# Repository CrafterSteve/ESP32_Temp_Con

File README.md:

# ESP32_Temp_Con
An temperture control device, based on ESP32. With custom PCB board, it can fit an ESP32-DevKit as controller, DAC and ADC is done on board, as well as, a 5 to +-12v power supply.

## Notes:
项目中 ./main/my_spiffs/ 目录下的文件会通过命令，全部烧写的分区 label 的 flash 中。

创建自定义空间前，先做配置：
used "idf.py menuconfig" to change partition table to csv.

created "partitions.csv" with 256KB of spiffs as "/storage": （以下是"partitions.csv"文件应该包含的内容）
nvs, data, nvs, 0x9000, 0x6000
phy_init, data, phy, 0xf000, 0x1000
factory, app, factory, 0x10000, 0x100000
storage, data, spiffs, 0x110000, 0x40000

## SPIFFS指令：
使用时注意 python 工具的路径。“./” 代表本项目的根目录

python D:\esp\v5.2.1\esp-idf\components\partition_table\gen_esp32part.py .\partitions.csv .\partitions.bin                                      // 从csv生成分区文件

idf.py partition-table-flash                                                                                                                    // 烧录分区文件

python D:\esp\v5.2.1\esp-idf\components\spiffs\spiffsgen.py 0x40000 D:\esp_projects\dactest_2.1\main\my_spiffs my_spiffs_img                    // 创建SPIFFS镜像文件

python D:\esp\v5.2.1\esp-idf\components\partition_table\parttool.py -p COM3 write_partition --partition-name storage --input .\my_spiffs_img    // 写入esp32

## 程序调用
in code: base_path = "/storage"     // esp32内文件目录
"/storage/bmp_test.bmp" 为存入的文件
FILE *file = fopen("/storage/bmp_test.bmp", "rb");  // 如此打开flash上的文件
可通过 esp_spiffs_info(spiffs_conf.partition_label, &total, &used); 查看占用，检查是否写入。

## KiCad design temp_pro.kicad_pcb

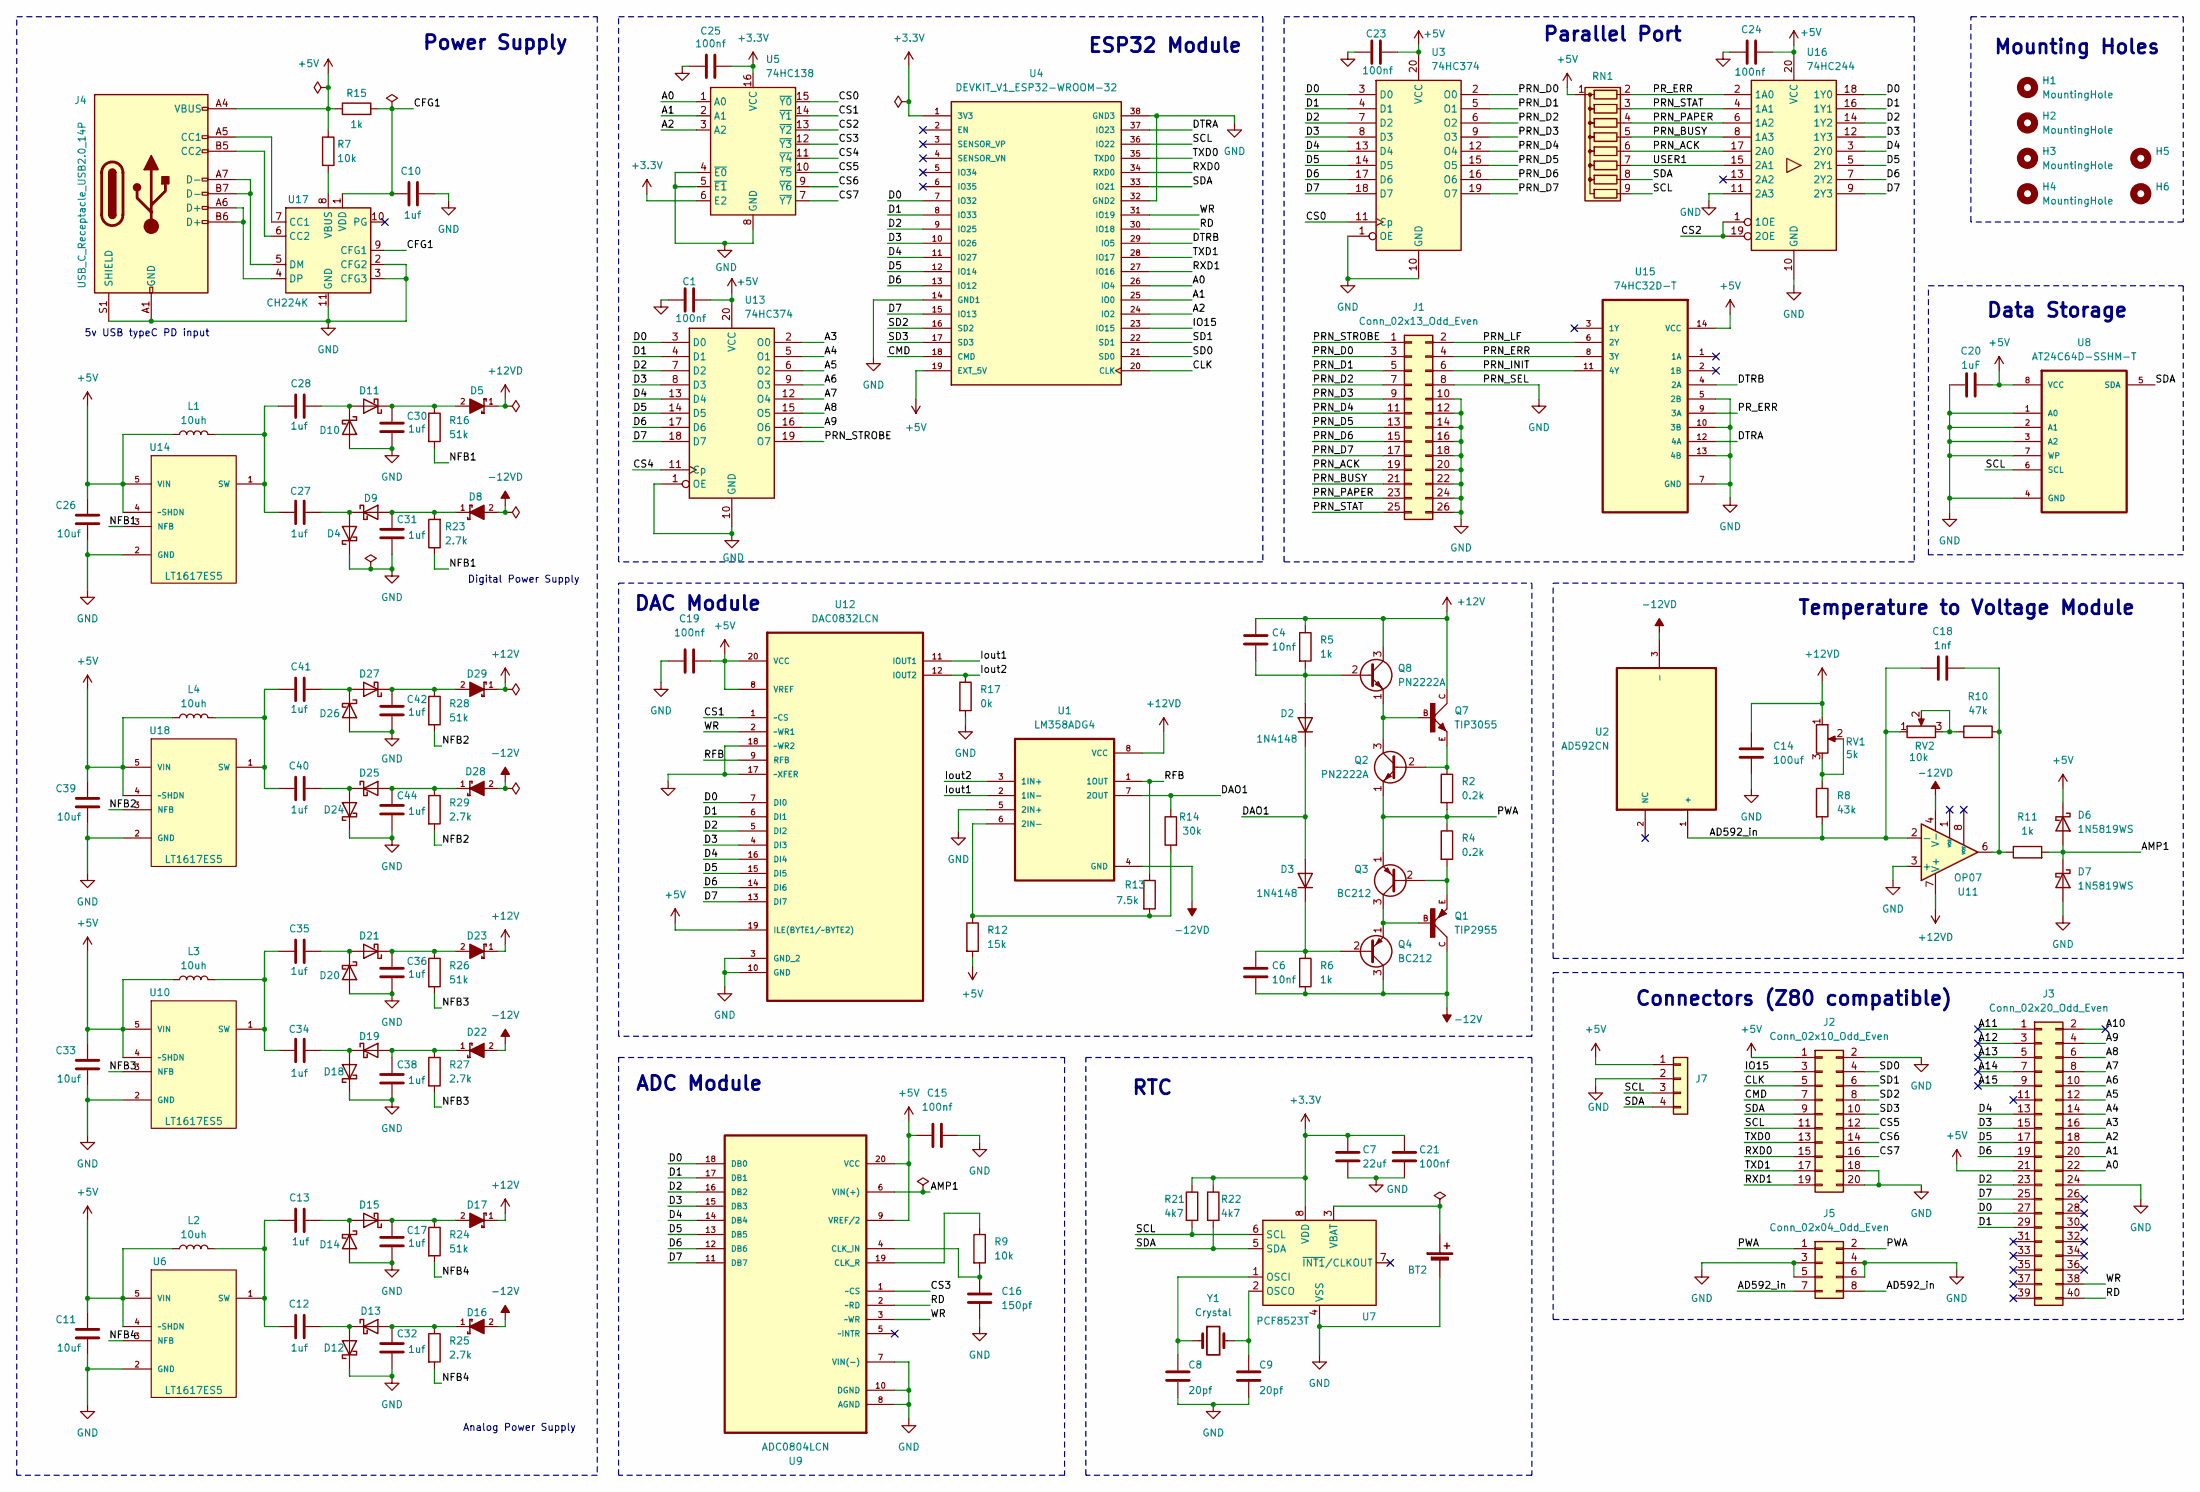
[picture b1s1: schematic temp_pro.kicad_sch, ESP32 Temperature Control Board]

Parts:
BT2: Battery_Cell; TE_796136-1
C1, C15, C19, C23, C24, C25: 100nf; C_0805_2012Metric
C4, C6: 10nf; C_Disc_D5.0mm_W2.5mm_P5.00mm
C7: 22uf; C_0805_2012Metric
C8, C9: 20pf; C_0805_2012Metric
C10: 1uf; C_0603_1608Metric
C11, C26, C33, C39: 10uf; C_0603_1608Metric
C12, C13, C17, C27, C28, C30, C31, C32, C34, C35, C36, C38, C40, C41, C42, C44: 1uf; C_0805_2012Metric
C14: 100uf; C_0805_2012Metric
C16: 150pf; C_0603_1608Metric
C18: 1nf; C_0805_2012Metric
C20: 1uF; C_0603_1608Metric
C21: 100nf; C_0603_1608Metric
D2, D3: 1N4148; D_DO-35_SOD27_P7.62mm_Horizontal
D4, D9, D10, D11, D12, D13, D14, D15, D18, D19, D20, D21, D24, D25, D26, D27: 1N5822; DIOM5025X220N
D5, D8, D16, D17, D22, D23, D28, D29: SS54-HF; DIOM5025X220N; MOUSER_PART_NUMBER 750-SS54-HF
D6, D7: 1N5819WS; D_SOD-323_HandSoldering
H1, H2, H3, H4, H5, H6: MountingHole; MountingHole_3.2mm_M3_ISO14580
J1: Conn_02x13_Odd_Even; PinHeader_2x13_P2.54mm_Vertical
J2: Conn_02x10_Odd_Even; PinHeader_2x10_P2.54mm_Vertical
J3: Conn_02x20_Odd_Even; PinHeader_2x20_P2.54mm_Vertical
J4: USB_C_Receptacle_USB2.0_14P; USB_C_Receptacle_GCT_USB4105-xx-A_16P_TopMnt_Horizontal
J5: Conn_02x04_Odd_Even; PinHeader_2x04_P2.54mm_Vertical
J7: Conn_01x04; PinHeader_1x04_P2.54mm_Vertical
L1, L2, L3, L4: 10uh; L_Bourns_SRP7028A_7.3x6.6mm
Q1: TIP2955; TOP3AV
Q2, Q8: PN2222A; TO-92_Inline
Q3, Q4: BC212; TO-92_Inline
Q7: TIP3055; TOP3AV
R2, R4: 0.2k; R_Axial_DIN0516_L15.5mm_D5.0mm_P20.32mm_Horizontal
R5, R6: 1k; R_Axial_DIN0207_L6.3mm_D2.5mm_P7.62mm_Horizontal
R7, R9: 10k; R_0603_1608Metric
R8: 43k; R_0805_2012Metric
R10: 47k; R_0805_2012Metric
R11, R15: 1k; R_0805_2012Metric
R12: 15k; R_0805_2012Metric
R13: 7.5k; R_0805_2012Metric
R14: 30k; R_0805_2012Metric
R16, R24, R26, R28: 51k; R_0603_1608Metric
R17: 0k; R_0603_1608Metric
R21, R22: 4k7; R_0603_1608Metric
R23, R25, R27, R29: 2.7k; R_0603_1608Metric
RN1: R_Network08; R_Array_SIP9
RV1: 5k; Potentiometer_Vishay_T93YA_Vertical
RV2: 10k; Potentiometer_Vishay_T93YA_Vertical
U1: LM358ADG4; DIP-8_W7.62mm_Socket
U2: AD592CN; TO-92L; MPN AD592CN
U3, U13: 74HC374; DIP-20_W7.62mm_Socket
U4: DEVKIT_V1_ESP32-WROOM-32; MODULE_DEVKIT_V1_ESP32-WROOM-32; PARTREV N/A
U5: 74HC138; DIP-16_W7.62mm_Socket
U6, U10, U14, U18: LT1617ES5; SOT-23-6; MPN LT1617ES5#PBF
U7: PCF8523T; SOIC-8_3.9x4.9mm_P1.27mm
U8: AT24C64D-SSHM-T; DIP-8_W7.62mm_Socket; MPN AT24C64D-SSHM-T
U9: ADC0804LCN; DIP-20_W7.62mm_Socket; MPN ADC0804LCN
U11: OP07; DIP-8_W7.62mm_Socket
U12: DAC0832LCN; DIP-20_W7.62mm_Socket; MPN DAC0832LCN
U15: 74HC32D-T; DIP-14_W7.62mm_Socket; MPN 74HC32D-T
U16: 74HC244; DIP-20_W7.62mm_Socket
U17: CH224K; SSOP-10-1EP_3.9x4.9mm_P1mm_EP2.1x3.3mm
Y1: Crystal; Crystal_C38-LF_D3.0mm_L8.0mm_Horizontal

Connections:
+3.3V: C7.1, C21.1, C25.2, R21.1, R22.1, U4.1 (3V3), U5.6 (E2), U5.16 (VCC), U7.8 (VDD)
+5V: C1.2, C11.1, C15.2, C19.2, C20.2, C23.2, C24.2, C26.1, C33.1, C39.1, D6.1 (K), J2.1, J3.21, J4.A4 (VBUS), J4.A9 (VBUS), J4.B4 (VBUS), J4.B9 (VBUS), J7.1, L1.1, L2.1, L3.1, L4.1, R7.1, R12.2, R15.1, RN1.1 (common), U3.20 (VCC), U4.19 (EXT_5V), U6.4 (~SHDN), U6.5 (VIN), U8.8 (VCC), U9.9 (VREF/2), U9.20 (VCC), U10.4 (~SHDN), U10.5 (VIN), U12.8 (VREF), U12.19 (ILE(BYTE1/~BYTE2)), U12.20 (VCC), U13.20 (VCC), U14.4 (~SHDN), U14.5 (VIN), U15.14 (VCC), U16.20 (VCC), U18.4 (~SHDN), U18.5 (VIN)
+12V: C4.1, D17.1, D23.1, D29.1, Q7.C, Q8.3 (C), R5.1
+12VD: C14.1, D5.1, RV1.1, U1.8 (VCC), U11.7 (V+)
-12V: C6.2, D16.2, D22.2, D28.2, Q1.C, Q4.3 (C), R6.2
-12VD: D8.2, U1.4 (GND), U2.3 (-), U11.4 (V-)
/A0: J3.22, U4.26 (IO4), U5.1 (A0)
/A1: J3.20, U4.25 (IO0), U5.2 (A1)
/A2: J3.18, U4.24 (IO2), U5.3 (A2)
/A3: J3.16, U13.2 (O0)
/A4: J3.14, U13.5 (O1)
/A5: J3.12, U13.6 (O2)
/A6: J3.10, U13.9 (O3)
/A7: J3.8, U13.12 (O4)
/A8: J3.6, U13.15 (O5)
/A9: J3.4, U13.16 (O6)
/A10: J3.2
/A11: J3.1
/A12: J3.3
/A13: J3.5
/A14: J3.7
/A15: J3.9
/AD592_in: C18.1, J5.7, J5.8, R8.2, RV2.1, U2.1 (+), U11.2 (-)
/AMP1: D6.2 (A), D7.1 (K), R11.2, U9.6 (VIN(+))
/CFG1: C10.1, R15.2, U17.1 (VDD), U17.9 (CFG1)
/CLK: J2.5, U4.20 (CLK)
/CMD: J2.7, U4.18 (CMD)
/CS0: U3.11 (Cp), U5.15 (~Y0)
/CS1: U5.14 (~Y1), U12.1 (~CS)
/CS2: U5.13 (~Y2), U16.1 (1OE), U16.19 (2OE)
/CS3: U5.12 (~Y3), U9.1 (~CS)
/CS4: U5.11 (~Y4), U13.11 (Cp)
/CS5: J2.12, U5.10 (~Y5)
/CS6: J2.14, U5.9 (~Y6)
/CS7: J2.16, U5.7 (~Y7)
/D0: J3.27, U3.3 (D0), U4.7 (IO32), U9.18 (DB0), U12.7 (DI0), U13.3 (D0), U16.18 (1Y0)
/D1: J3.29, U3.4 (D1), U4.8 (IO33), U9.17 (DB1), U12.6 (DI1), U13.4 (D1), U16.16 (1Y1)
/D2: J3.23, U3.7 (D2), U4.9 (IO25), U9.16 (DB2), U12.5 (DI2), U13.7 (D2), U16.14 (1Y2)
/D3: J3.15, U3.8 (D3), U4.10 (IO26), U9.15 (DB3), U12.4 (DI3), U13.8 (D3), U16.12 (1Y3)
/D4: J3.13, U3.13 (D4), U4.11 (IO27), U9.14 (DB4), U12.16 (DI4), U13.13 (D4), U16.3 (2Y0)
/D5: J3.17, U3.14 (D5), U4.12 (IO14), U9.13 (DB5), U12.15 (DI5), U13.14 (D5), U16.5 (2Y1)
/D6: J3.19, U3.17 (D6), U4.13 (IO12), U9.12 (DB6), U12.14 (DI6), U13.17 (D6), U16.7 (2Y2)
/D7: J3.25, U3.18 (D7), U4.15 (IO13), U9.11 (DB7), U12.13 (DI7), U13.18 (D7), U16.9 (2Y3)
/DAO1: D2.1 (K), D3.2 (A), R14.1, U1.7 (2OUT)
/DTRA: U4.37 (IO23), U15.12 (4A)
/DTRB: U4.29 (IO5), U15.4 (2A)
/IO15: J2.3, U4.23 (IO15)
/Iout1: U1.2 (1IN-), U12.11 (IOUT1)
/Iout2: R17.1, U1.3 (1IN+), U12.12 (IOUT2)
/NFB1: R16.2, R23.1, U14.3 (NFB)
/NFB2: R28.2, R29.2, U18.3 (NFB)
/NFB3: R26.2, R27.2, U10.3 (NFB)
/NFB4: R24.2, R25.2, U6.3 (NFB)
/PRN_ACK: J1.19, RN1.6 (R5), U16.17 (2A0)
/PRN_BUSY: J1.21, RN1.5 (R4), U16.8 (1A3)
/PRN_D0: J1.3, U3.2 (O0)
/PRN_D1: J1.5, U3.5 (O1)
/PRN_D2: J1.7, U3.6 (O2)
/PRN_D3: J1.9, U3.9 (O3)
/PRN_D4: J1.11, U3.12 (O4)
/PRN_D5: J1.13, U3.15 (O5)
/PRN_D6: J1.15, U3.16 (O6)
/PRN_D7: J1.17, U3.19 (O7)
/PRN_ERR: J1.4, U15.8 (3Y)
/PRN_INIT: J1.6, U15.11 (4Y)
/PRN_LF: J1.2, U15.6 (2Y)
/PRN_PAPER: J1.23, RN1.4 (R3), U16.6 (1A2)
/PRN_STAT: J1.25, RN1.3 (R2), U16.4 (1A1)
/PRN_STROBE: J1.1, U13.19 (O7)
/PR_ERR: RN1.2 (R1), U15.9 (3A), U16.2 (1A0)
/PWA: J5.1, J5.2, Q2.1 (E), Q3.1 (E), R2.2, R4.1
/RD: J3.40, U4.30 (IO18), U9.2 (~RD)
/RFB: R13.1, U1.1 (1OUT), U12.9 (RFB)
/RXD0: J2.15, U4.34 (RXD0)
/RXD1: J2.19, U4.27 (IO16)
/SCL: J2.11, J7.3, R21.2, RN1.9 (R8), U4.36 (IO22), U7.6 (SCL), U8.6 (SCL)
/SD0: J2.4, U4.21 (SD0)
/SD1: J2.6, U4.22 (SD1)
/SD2: J2.8, U4.16 (SD2)
/SD3: J2.10, U4.17 (SD3)
/SDA: J2.9, J7.4, R22.2, RN1.8 (R7), U4.33 (IO21), U7.5 (SDA), U8.5 (SDA)
/TXD0: J2.13, U4.35 (TXD0)
/TXD1: J2.17, U4.28 (IO17)
/USER1: RN1.7 (R6), U16.15 (2A1)
/WR: J3.38, U4.31 (IO19), U9.3 (~WR), U12.2 (~WR1)
GND: BT2.2 (-), C1.1, C7.2, C8.2, C9.2, C10.2, C11.2, C14.2, C15.1, C16.2, C17.2, C19.1, C20.1, C21.2, C23.1, C24.1, C25.1, C26.2, C30.2, C31.2, C32.2, C33.2, C36.2, C38.2, C39.2, C42.2, C44.2, D4.1 (K), D7.2 (A), D10.2 (A), D12.1 (K), D14.2 (A), D18.1 (K), D20.2 (A), D24.1 (K), D26.2 (A), J1.8, J1.10, J1.12, J1.14, J1.16, J1.18, J1.20, J1.22, J1.24, J1.26, J2.2, J2.18, J2.20, J3.24, J4.A1 (GND), J4.A12 (GND), J4.B1 (GND), J4.B12 (GND), J4.S1 (SHIELD), J5.3, J5.4, J5.5, J5.6, J7.2, R17.2, U1.5 (2IN+), U3.1 (OE), U3.10 (GND), U4.14 (GND1), U4.32 (GND2), U4.38 (GND3), U5.4 (~E0), U5.5 (~E1), U5.8 (GND), U6.2 (GND), U7.4 (VSS), U8.1 (A0), U8.2 (A1), U8.3 (A2), U8.4 (GND), U8.7 (WP), U9.7 (VIN(-)), U9.8 (AGND), U9.10 (DGND), U10.2 (GND), U11.3 (+), U12.3 (GND_2), U12.10 (GND), U12.17 (~XFER), U12.18 (~WR2), U13.1 (OE), U13.10 (GND), U14.2 (GND), U15.5 (2B), U15.7 (GND), U15.10 (3B), U15.13 (4B), U16.10 (GND), U16.11 (2A3), U17.2 (CFG2), U17.3 (CFG3), U17.11 (GND), U18.2 (GND)
unnamed: BT2.1 (+), U7.3 (VBAT)
unnamed: C18.2, R10.2, R11.1, U11.6
unnamed: C4.2, D2.2 (A), Q8.2 (B), R5.2
unnamed: C6.1, D3.1 (K), Q4.2 (B), R6.1
unnamed: C27.2, D4.2 (A), D9.1 (K)
unnamed: C31.1, D8.1, D9.2 (A), R23.2
unnamed: C28.1, D10.1 (K), D11.2 (A)
unnamed: C30.1, D5.2, D11.1 (K), R16.1
unnamed: C12.2, D12.2 (A), D13.1 (K)
unnamed: C32.1, D13.2 (A), D16.1, R25.1
unnamed: C13.1, D14.1 (K), D15.2 (A)
unnamed: C17.1, D15.1 (K), D17.2, R24.1
unnamed: C34.2, D18.2 (A), D19.1 (K)
unnamed: C38.1, D19.2 (A), D22.1, R27.1
unnamed: C35.1, D20.1 (K), D21.2 (A)
unnamed: C36.1, D21.1 (K), D23.2, R26.1
unnamed: C40.2, D24.2 (A), D25.1 (K)
unnamed: C44.1, D25.2 (A), D28.1, R29.1
unnamed: C41.1, D26.1 (K), D27.2 (A)
unnamed: C42.1, D27.1 (K), D29.2, R28.1
unnamed: J4.A5 (CC1), U17.7 (CC1)
unnamed: J4.B5 (CC2), U17.6 (CC2)
unnamed: Q2.2 (B), Q7.E, R2.1
unnamed: Q2.3 (C), Q7.B, Q8.1 (E)
unnamed: Q1.E, Q3.2 (B), R4.2
unnamed: Q1.B, Q3.3 (C), Q4.1 (E)
unnamed: R8.1, RV1.2, RV1.3
unnamed: R10.1, RV2.2, RV2.3
unnamed: R12.1, R13.2, R14.2, U1.6 (2IN-)
unnamed: C12.1, C13.2, L2.2, U6.1 (SW)
unnamed: C8.1, U7.1 (OSCI), Y1.1
unnamed: C9.1, U7.2 (OSCO), Y1.2
unnamed: C16.1, R9.2, U9.4 (CLK_IN)
unnamed: R9.1, U9.19 (CLK_R)
unnamed: C34.1, C35.2, L3.2, U10.1 (SW)
unnamed: C27.1, C28.2, L1.2, U14.1 (SW)
unnamed: J4.A7 (D-), J4.B7 (D-), U17.5 (DM)
unnamed: J4.A6 (D+), J4.B6 (D+), U17.4 (DP)
unnamed: R7.2, U17.8 (VBUS)
unnamed: C40.1, C41.2, L4.2, U18.1 (SW)

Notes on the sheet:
5v USB typeC PD input
ESP32 Module
Digital Power Supply
Data Storage
ADC Module
RTC
Temperature to Voltage Module
DAC Module
Mounting Holes
Parallel Port
Analog Power Supply
Power Supply
Connectors (Z80 compatible)

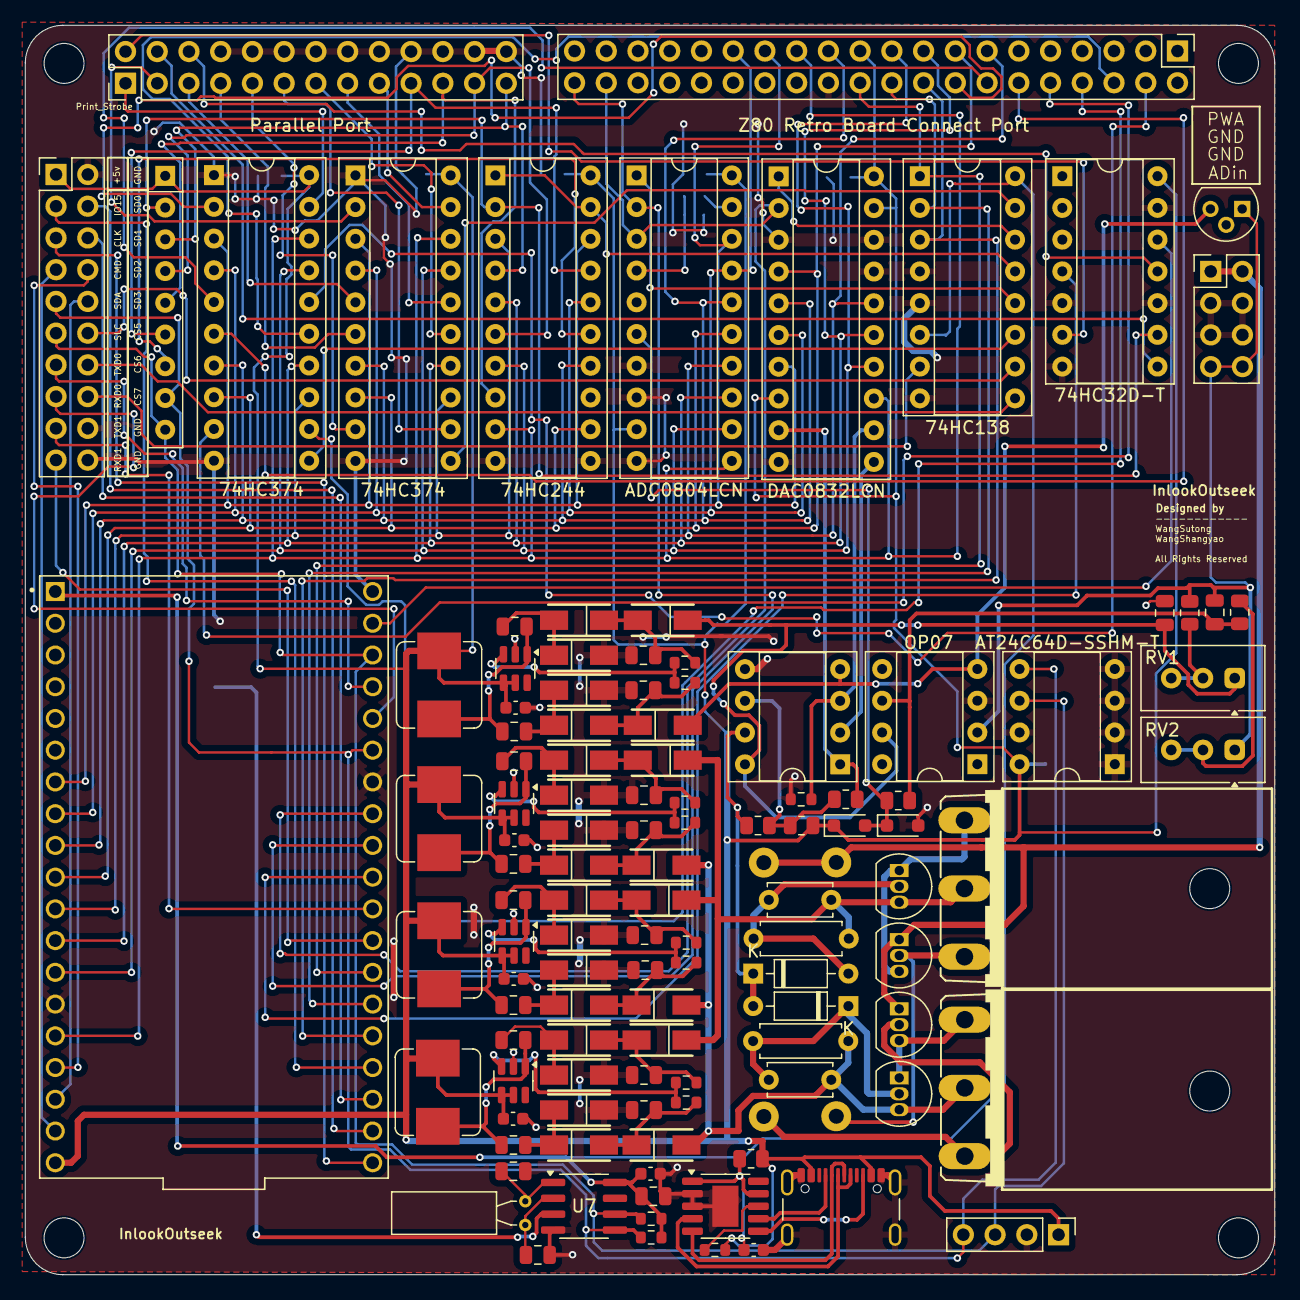
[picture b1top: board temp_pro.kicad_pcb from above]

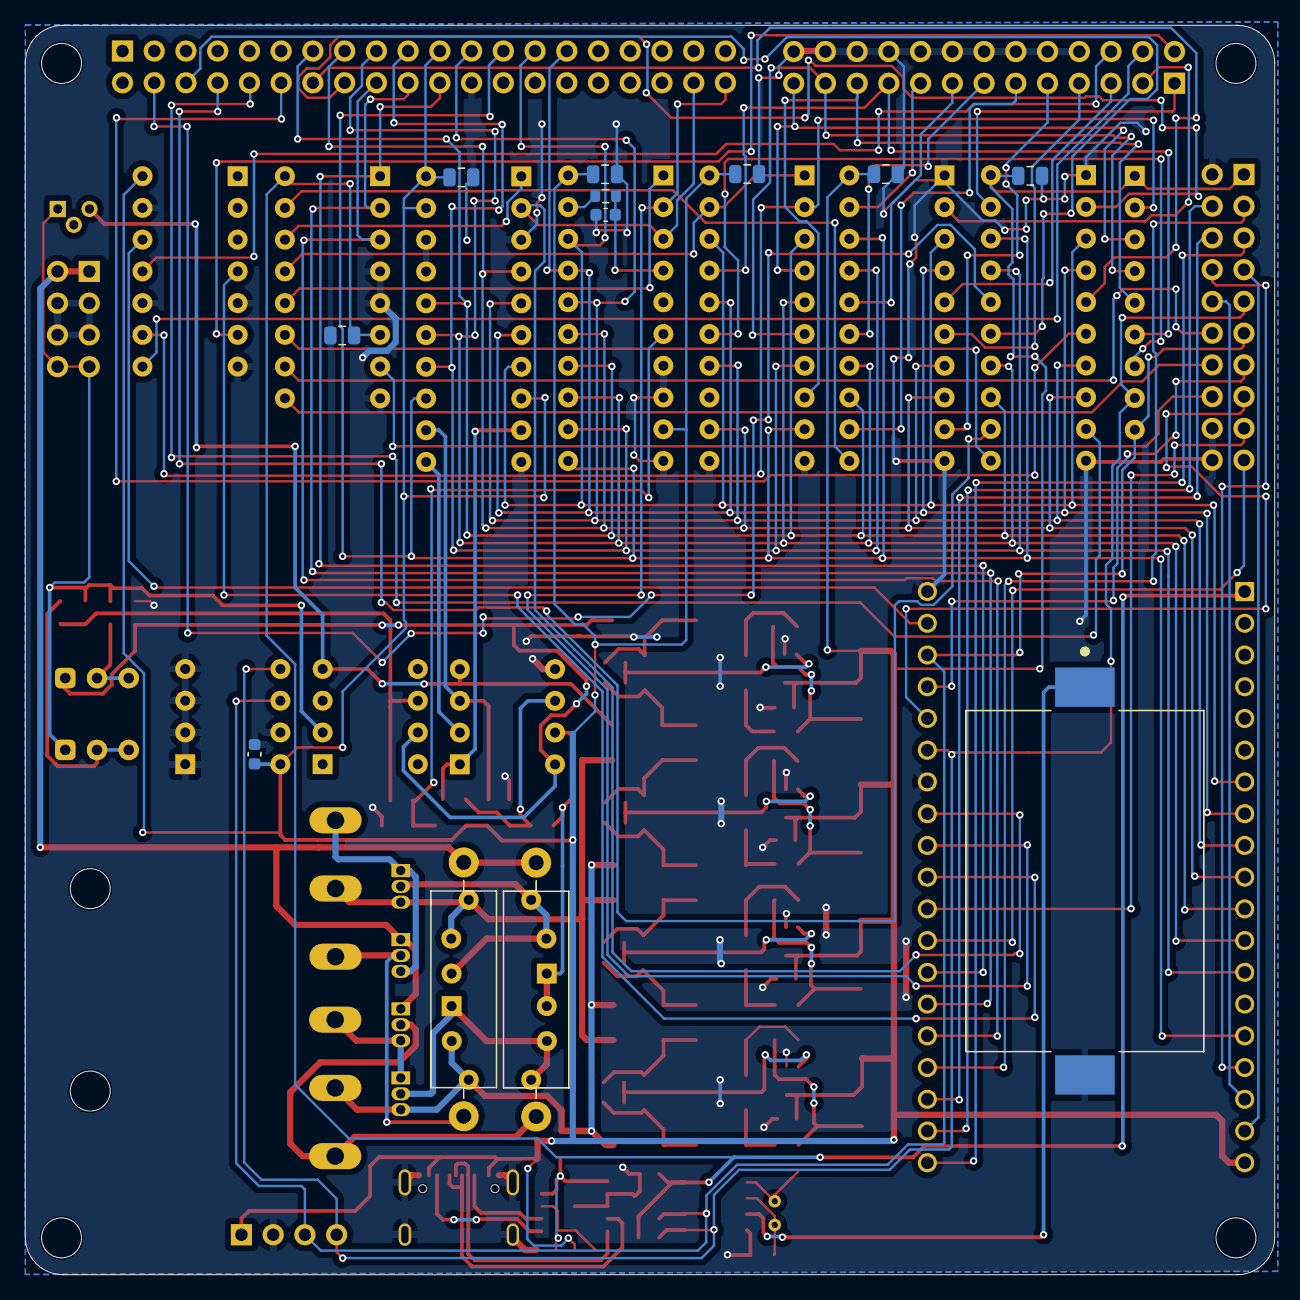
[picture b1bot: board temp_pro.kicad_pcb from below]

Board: 2 copper layers, 100.0 x 100.0 mm, 134 parts (12 on the bottom side), 120 nets.

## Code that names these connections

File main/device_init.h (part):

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#define A2  2

//Printer
#define PRN_STROBE  D7
#define PRN_ERR     D0
#define PRN_STAT    D1
#define PRN_PAPER   D2
#define PRN_BUSY    D3
#define PRN_ACK     D4

//I2C Bus
#define SCL 22
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
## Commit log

2025-03-27 Functional codes with basic functions.
2025-03-28 PCB files, still bugs to be fixed in next version

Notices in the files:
temp_pro.kicad_pcb:
All Rights Reserved
